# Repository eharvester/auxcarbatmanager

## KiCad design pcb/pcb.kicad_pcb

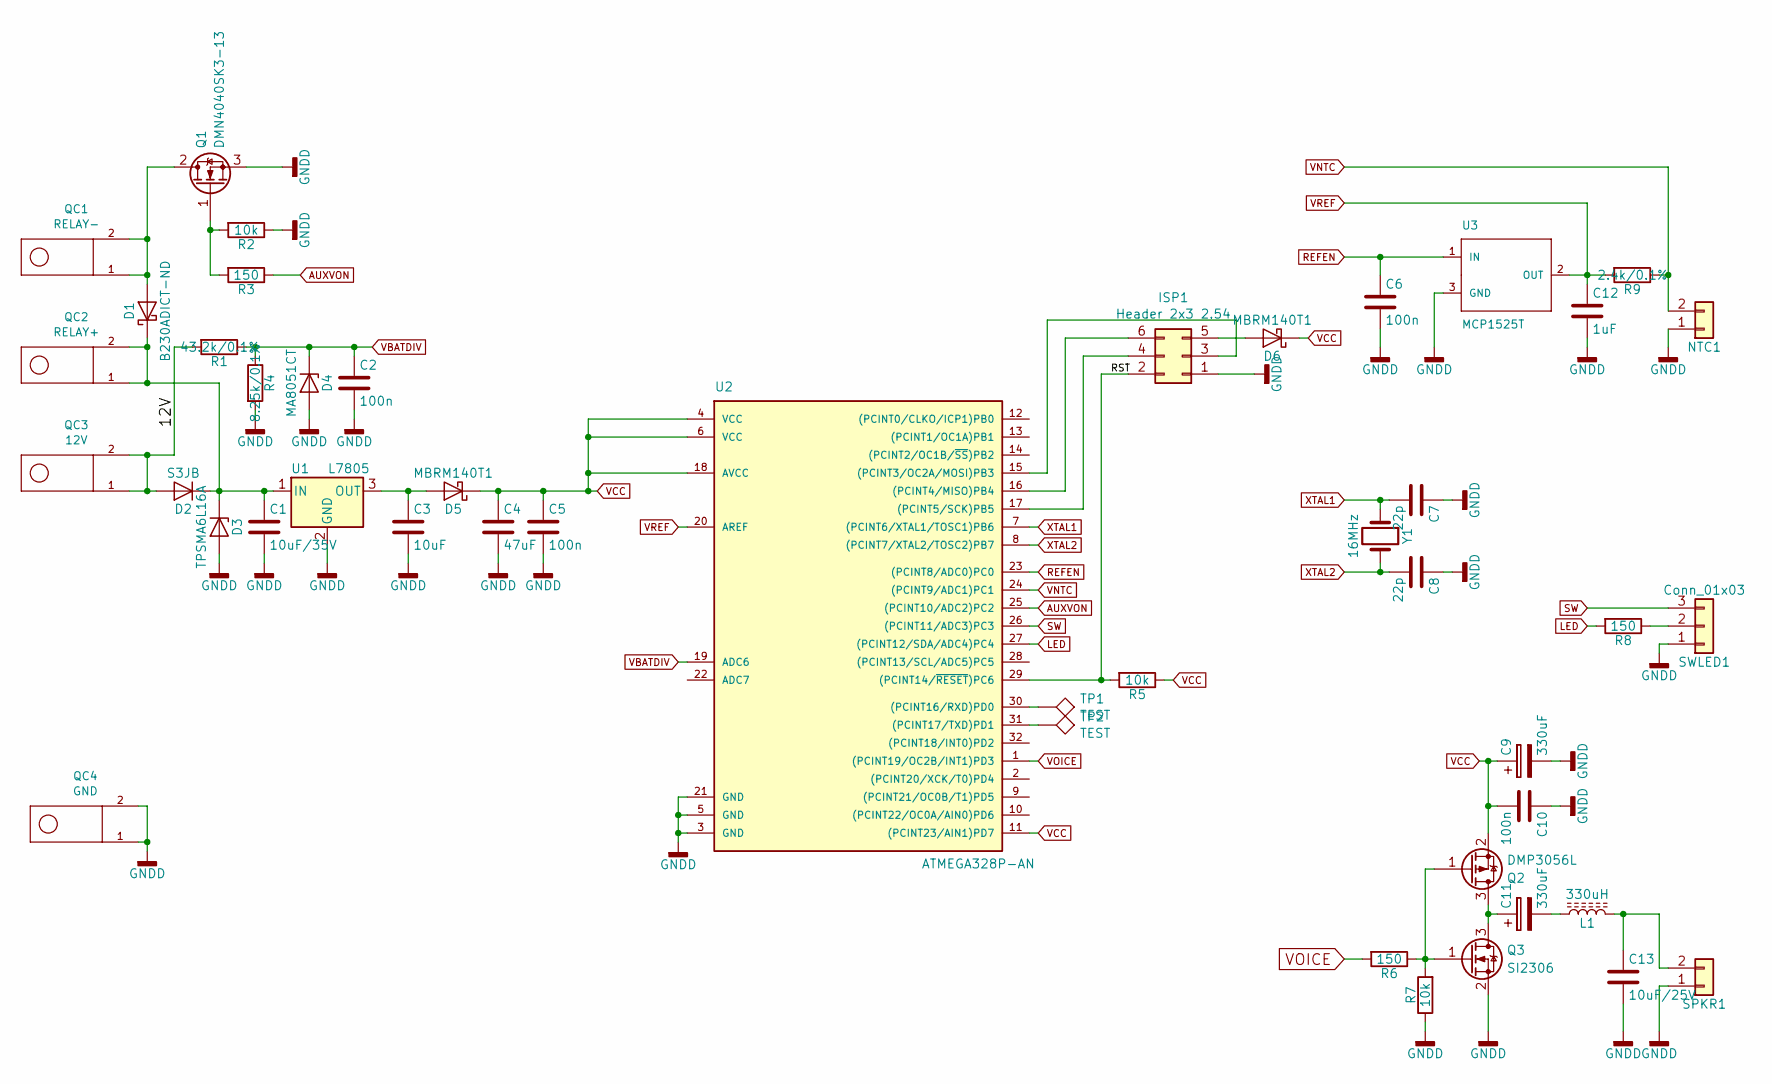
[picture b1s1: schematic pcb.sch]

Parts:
C1: 10uF/35V; C_1206
C2, C5, C6, C10: 100n; C_0603
C3: 10uF; C_0805
C4: 47uF; C_0805
C7, C8: 22p; C_0603
C9, C11: 330uF; CP_Radial_D10.0mm_P5.00mm
C12: 1uF; C_0603
C13: 10uF/25V; C_0805
D1: B230ADICT-ND; D_SMB
D2: S3JB; D_SMB
D3: TPSMA6L16A; D_SMA
D4: MA8051CT; D_SOD-323
D5, D6: MBRM140T1; D_Powermite_AK
ISP1: Header 2x3 2.54; Pin_Header_Straight_2x03_Pitch2.54mm
L1: 330uH; L_Radial_D10.0mm_P5.00mm_Fastron_07M
NTC1: Conn_01x02; JST_XH_B02B-XH-A_02x2.50mm_Straight
Q1: DMN4040SK3-13; TO-252-2
Q2: DMP3056L; SOT-23
Q3: SI2306; SOT-23
QC1: RELAY-; QUICKCONNECT-TAB-6.35X0.81
QC2: RELAY+; QUICKCONNECT-TAB-6.35X0.81
QC3: 12V; QUICKCONNECT-TAB-6.35X0.81
QC4: GND; QUICKCONNECT-TAB-6.35X0.81
R1: 43.2k/0.1%; R_0603
R2, R5, R7: 10k; R_0603
R3, R6, R8: 150; R_0603
R4: 8.25k/0.1%; R_0603
R9: 2.4k/0.1%; R_0603
SPKR1: Conn_01x02; JST_XH_B02B-XH-A_02x2.50mm_Straight
SWLED1: Conn_01x03; JST_XH_B03B-XH-A_03x2.50mm_Straight
TP1, TP2: TEST; Pin_Header_Straight_1x01_Pitch2.54mm
U1: L7805; TO-252-2
U2: ATMEGA328P-AN; TQFP-32_7x7mm_Pitch0.8mm
U3: MCP1525T; SOT-23
Y1: 16MHz; Crystal_HC18-U_Vertical

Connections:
/12V: D2.2 (A), QC3.1, QC3.2, R1.2
/RST: ISP1.2, R5.2, U2.29 ((PCINT14/~RESET~)PC6)
AUXVON: R3.1, U2.25 ((PCINT10/ADC2)PC2)
GNDD: C1.2, C2.2, C3.2, C4.2, C5.2, C6.2, C7.1, C8.1, C9.2, C10.1, C12.2, C13.2, D3.2 (A), D4.2 (A), ISP1.1, NTC1.1, Q1.3 (S), Q3.2 (S), QC4.1, QC4.2, R2.1, R4.2, R7.1, SPKR1.1, SWLED1.1, U1.2 (GND), U2.3 (GND), U2.5 (GND), U2.21 (GND), U3.3 (GND)
LED: R8.2, U2.27 ((PCINT12/SDA/ADC4)PC4)
unnamed: C1.1, D1.1 (K), D2.1 (K), D3.1 (K), QC2.1, QC2.2, U1.1 (IN)
unnamed: C3.1, D5.2 (A), U1.3 (OUT)
unnamed: C11.1, Q2.3 (D), Q3.3 (D)
unnamed: C11.2, L1.1
unnamed: C13.1, L1.2, SPKR1.2
unnamed: D1.2 (A), Q1.2 (D), QC1.1, QC1.2
unnamed: D6.2 (A), ISP1.5
unnamed: ISP1.3, U2.15 ((PCINT3/OC2A/MOSI)PB3)
unnamed: ISP1.4, U2.17 ((PCINT5/SCK)PB5)
unnamed: ISP1.6, U2.16 ((PCINT4/MISO)PB4)
unnamed: Q1.1 (G), R2.2, R3.2
unnamed: Q2.1 (G), Q3.1 (G), R6.1, R7.2
unnamed: R8.1, SWLED1.2
unnamed: TP1.1, U2.30 ((PCINT16/RXD)PD0)
unnamed: TP2.1, U2.31 ((PCINT17/TXD)PD1)
REFEN: C6.1, U2.23 ((PCINT8/ADC0)PC0), U3.1 (IN)
SW: SWLED1.3, U2.26 ((PCINT11/ADC3)PC3)
VBATDIV: C2.1, D4.1 (K), R1.1, R4.1, U2.19 (ADC6)
VCC: C4.1, C5.1, C9.1, C10.2, D5.1 (K), D6.1 (K), Q2.2 (S), R5.1, U2.4 (VCC), U2.6 (VCC), U2.11 ((PCINT23/AIN1)PD7), U2.18 (AVCC)
VNTC: NTC1.2, R9.1, U2.24 ((PCINT9/ADC1)PC1)
VOICE: R6.2, U2.1 ((PCINT19/OC2B/INT1)PD3)
VREF: C12.1, R9.2, U2.20 (AREF), U3.2 (OUT)
XTAL1: C7.2, U2.7 ((PCINT6/XTAL1/TOSC1)PB6), Y1.1
XTAL2: C8.2, U2.8 ((PCINT7/XTAL2/TOSC2)PB7), Y1.2

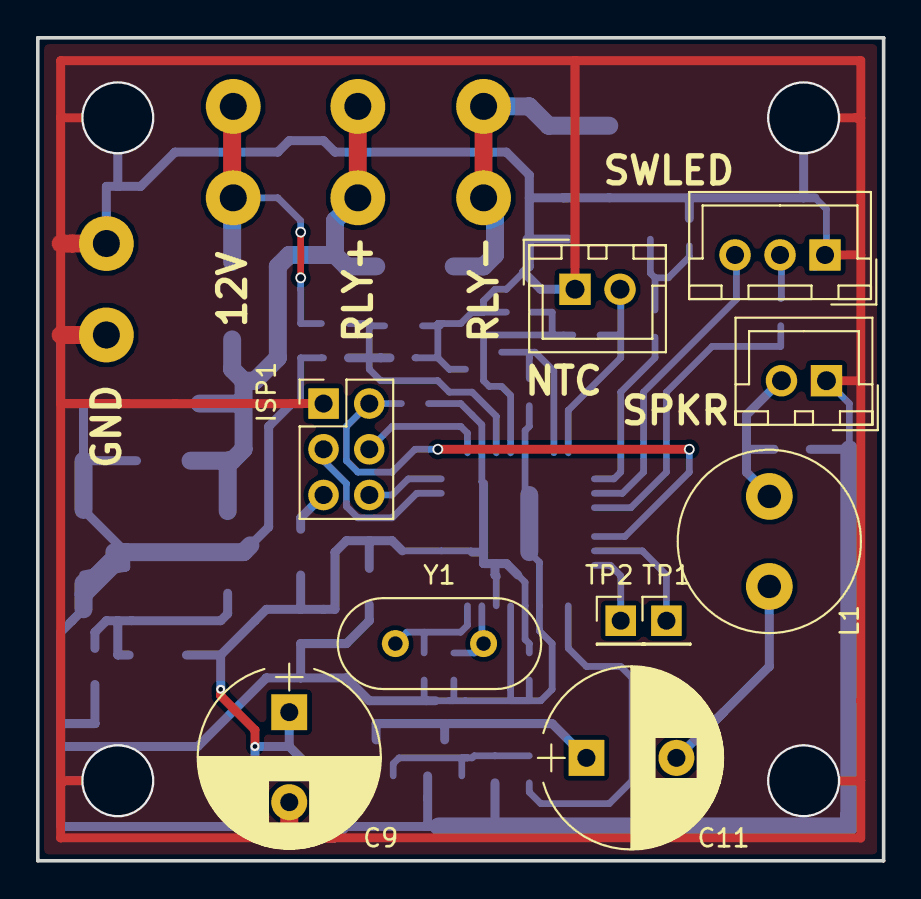
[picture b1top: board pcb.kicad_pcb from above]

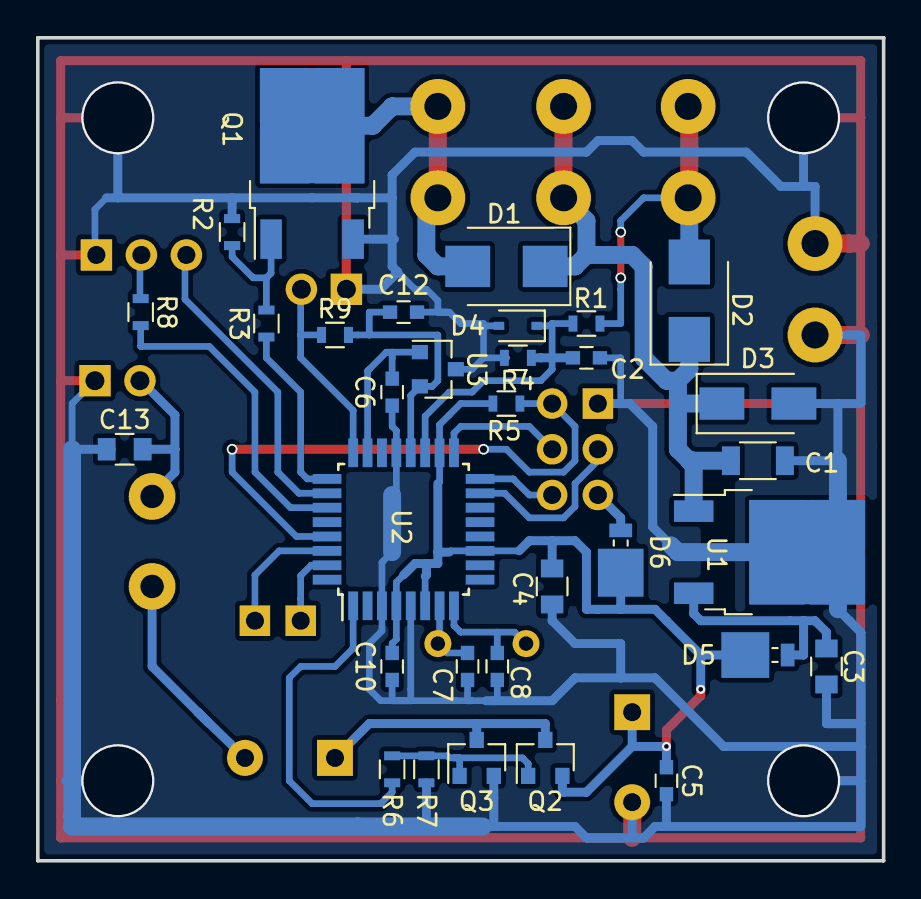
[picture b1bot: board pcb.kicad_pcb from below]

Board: 2 copper layers, 47.0 x 45.7 mm, 46 parts (32 on the bottom side), 29 nets.

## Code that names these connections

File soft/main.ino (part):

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// pin definitions
#define LED_PIN A4
#define SW_PIN A3
#define AUXVON_PIN A2 
#define NTC_PIN A1
#define REFEN_PIN A0 
#define VBATDIV_PIN A6 
#define VOICE_PIN 3
#define TX_PIN 1
#define RX_PIN 0

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#define LEDON digitalWrite(LED_PIN, HIGH)  
#define LEDOFF digitalWrite(LED_PIN, LOW) 

#define AUXON digitalWrite(AUXVON_PIN, HIGH)
#define AUXOFF digitalWrite(AUXVON_PIN,LOW)

#define VOICEOFFDELAY_MS 100

#define VOICEON pinMode(VOICE_PIN, OUTPUT) 
#define VOICEOFF {delay(VOICEOFFDELAY_MS); pinMode(VOICE_PIN, INPUT);} // disable drive to reduce power consumption

#define say(DATA) voice.say((uint8_t*)DATA) //progmen data are const but voice.say requires non-const

extern int temp(const unsigned char); 
extern int volts(const unsigned char); 
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
int getTemp (void) {
 int celsius;
 digitalWrite(REFEN_PIN, HIGH); // voltage reference on
 delay(ADCREFSETTLE_MS); // allow 1uF cap voltage to settle (measure!)
 celsius = temp(NTC_PIN);
 digitalWrite(REFEN_PIN, LOW); // voltage reference off
 return celsius;
}

int getTenthvolts (void) {
 int tenthvolts; 
 digitalWrite(REFEN_PIN, HIGH); // voltage reference on
 delay(ADCREFSETTLE_MS); // allow 1uF cap voltage to settle (measure!)
 tenthvolts = volts(VBATDIV_PIN);
 digitalWrite(REFEN_PIN, LOW); // voltage reference off
 return tenthvolts;
}

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 pinMode(TX_PIN,OUTPUT);
 digitalWrite(TX_PIN, LOW);

 pinMode(AUXVON_PIN,OUTPUT);
 digitalWrite(AUXVON_PIN, LOW);

 pinMode(REFEN_PIN,OUTPUT);
 digitalWrite(REFEN_PIN, LOW);
 analogReference(EXTERNAL);

#if VOICEDEBUG==1
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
